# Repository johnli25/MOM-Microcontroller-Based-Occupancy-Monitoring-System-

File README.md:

# Microcontroller-based Occupancy Monitoring (MOM)

### *Won ECE Senior Design Runner-Up Award* (Fall 2022)

## Authors and Acknowledgements
ECE 445 FA2022 Team 7:
- Franklin Moy
- Vish Gopal Sekar
- John Li
- TA: Hanyin Shao

## About
The goal of this project is to create a web app to allow users to determine how occupied popular study locations are.

## Repository Structure
- [**boards**](boards)
  - Contains KiCad project files for the hardware schematics and PCB layouts.
- [**code**](code)
  - Contains all software created for the project, including those used for RV processes and production code.
- [**models**](models)
  - Contains all custom symbols, footprints, and 3D models used for the hardware and enclosure design.
- [**notebooks**](notebooks)
  - Contains all individual lab notebooks.
 
## Paper/Report
[https://github.com/johnli25/MOM/blob/4fe8f952a4ed27d478e640dd72d3c75059fbbd7b/MOM%20Paper.pdf
](https://github.com/johnli25/MOM/blob/main/MOM%20Paper.pdf)
## The web app/dashboard

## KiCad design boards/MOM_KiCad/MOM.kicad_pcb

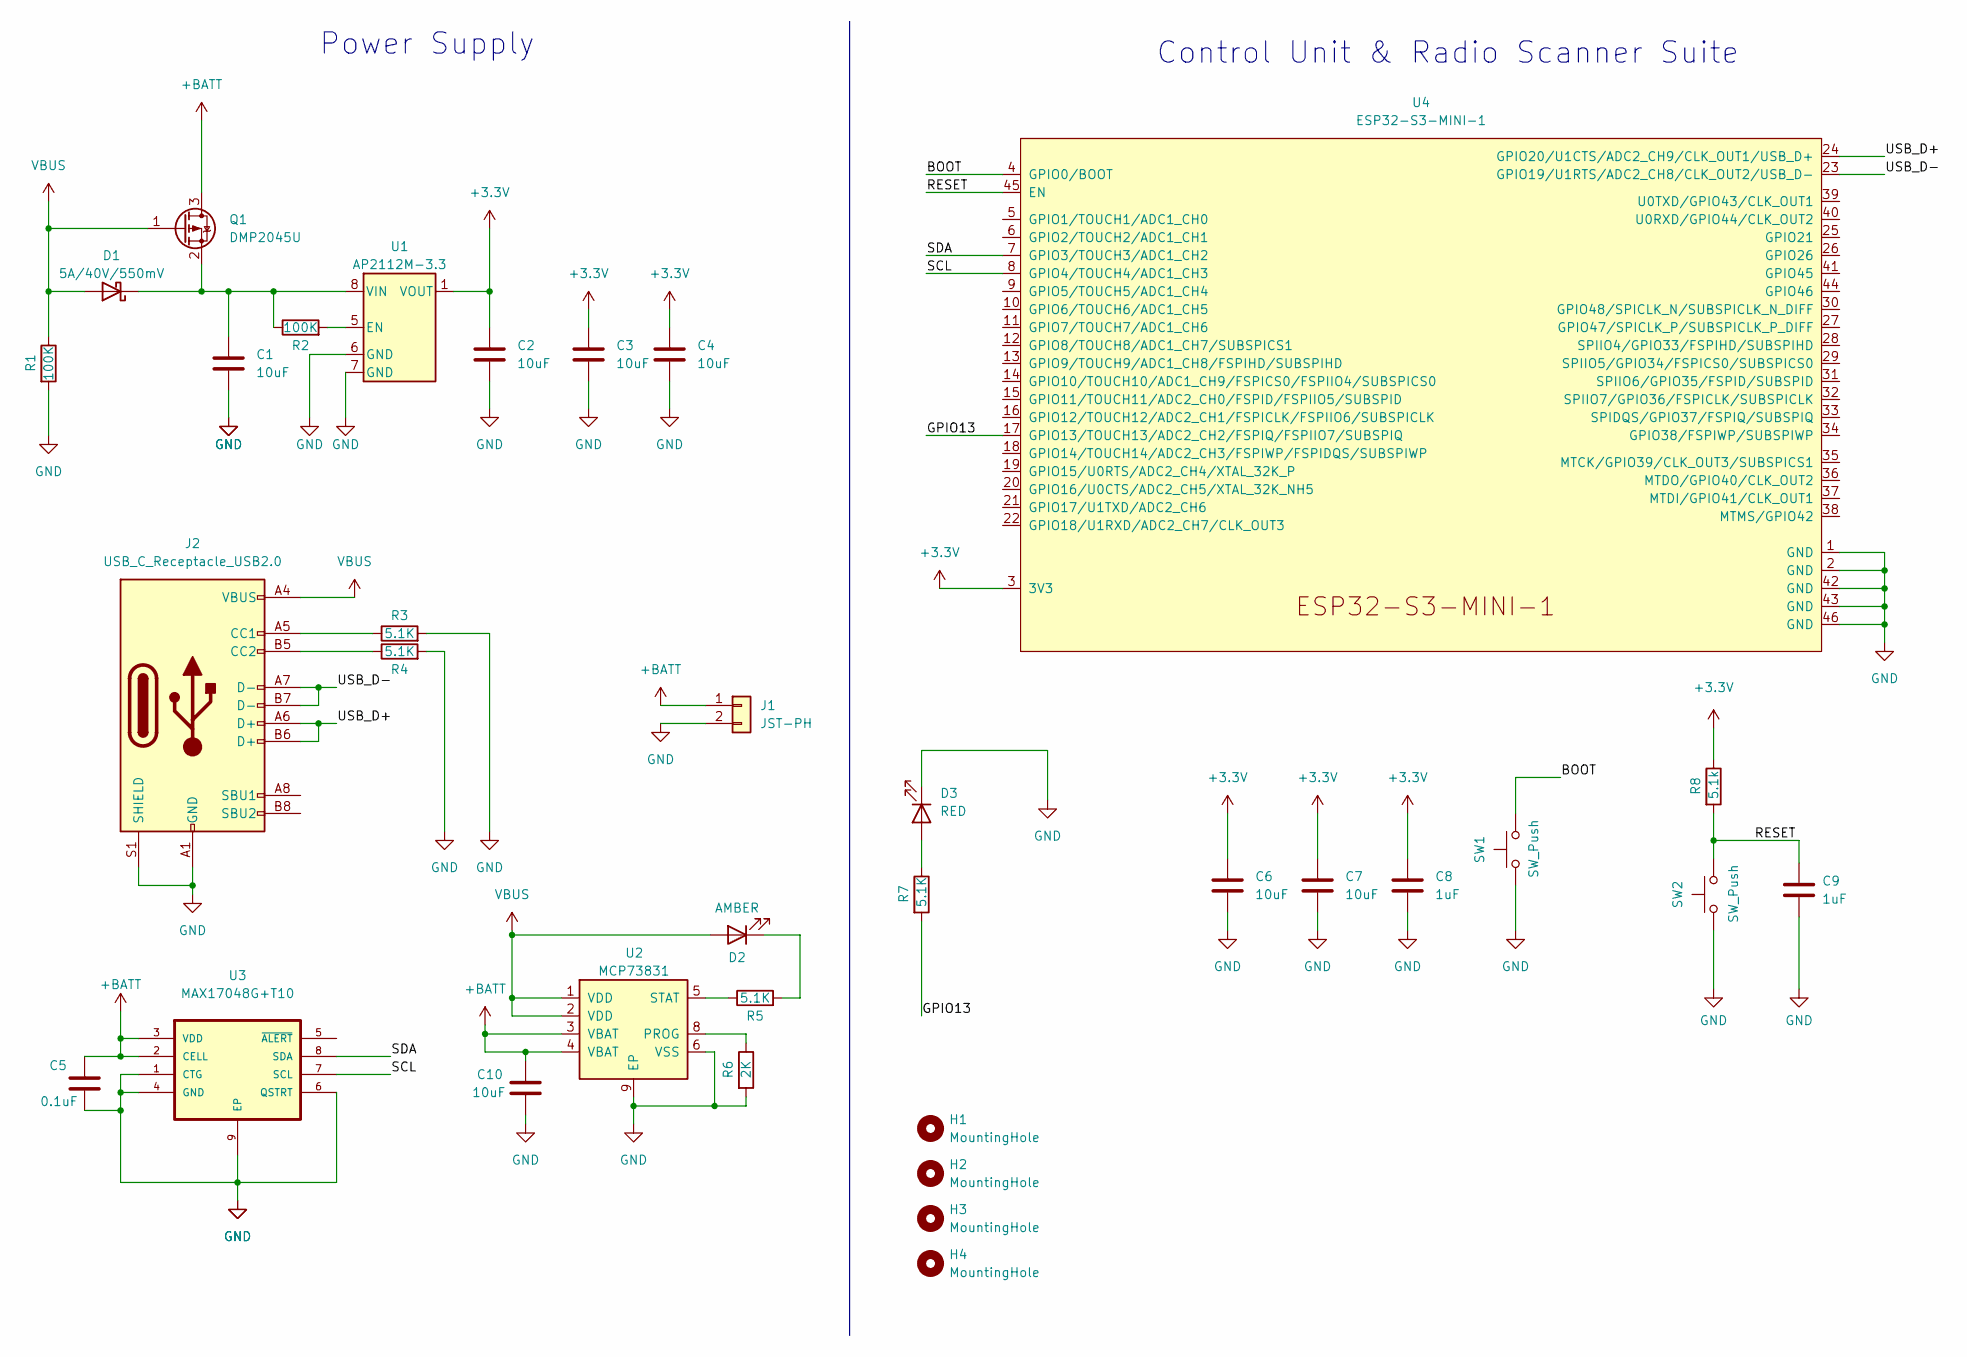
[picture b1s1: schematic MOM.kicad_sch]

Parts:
C1, C2, C3, C4, C6, C7, C10: 10uF; CP_EIA-2012-12_Kemet-R_Pad1.30x1.05mm_HandSolder
C5: 0.1uF; CP_EIA-2012-12_Kemet-R_Pad1.30x1.05mm_HandSolder
C8, C9: 1uF; CP_EIA-2012-12_Kemet-R_Pad1.30x1.05mm_HandSolder
D1: 5A/40V/550mV; D_SMBF_Handsoldering
D2: AMBER; LED_D5.0mm
D3: RED; LED_D5.0mm
H1, H2, H3, H4: MountingHole; MountingHole_3.2mm_M3
J1: JST-PH; JST_PH_S2B-PH-K_1x02_P2.00mm_Horizontal
J2: USB_C_Receptacle_USB2.0; USB_C_Receptacle_GCT_USB4085
Q1: DMP2045U; SOT-23_Handsoldering
R1, R2: 100K; R_1206_3216Metric_Pad1.30x1.75mm_HandSolder
R3, R4, R5, R7: 5.1K; R_1206_3216Metric_Pad1.30x1.75mm_HandSolder
R6: 2K; R_1206_3216Metric_Pad1.30x1.75mm_HandSolder
R8: 5.1k; R_1206_3216Metric_Pad1.30x1.75mm_HandSolder
SW1, SW2: SW_Push; SW_TS04-66-65-BK-160-SMT
U1: AP2112M-3.3; Diodes_SO-8
U2: MCP73831; SON50P200X300X100-9N
U3: MAX17048G+T10; SON50P200X200X80-9N
U4: ESP32-S3-MINI-1

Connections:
+3.3V: C2.1, C3.1, C4.1, C6.1, C7.1, C8.1, R8.1, U1.1 (VOUT), U4.3 (3V3)
+BATT: C5.1, C10.1, J1.1, Q1.3 (D), U2.3 (VBAT), U2.4 (VBAT), U3.2 (CELL), U3.3 (VDD)
/BOOT: SW1.2, U4.4 (GPIO0/BOOT)
/GPIO13: R7.2, U4.17 (GPIO13/TOUCH13/ADC2_CH2/FSPIQ/FSPIIO7/S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)
/RESET: C9.1, R8.2, SW2.2, U4.45 (EN)
/SCL: U3.7 (SCL), U4.8 (GPIO4/TOUCH4/ADC1_CH3)
/SDA: U3.8 (SDA), U4.7 (GPIO3/TOUCH3/ADC1_CH2)
/USB_D+: J2.A6 (D+), J2.B6 (D+), U4.24 (GPIO20/U1CTS/ADC2_CH9/CLK_OUT1/USB_D+)
/USB_D-: J2.A7 (D-), J2.B7 (D-), U4.23 (GPIO19/U1RTS/ADC2_CH8/CLK_OUT2/USB_D-)
GND: C1.2, C2.2, C3.2, C4.2, C5.2, C6.2, C7.2, C8.2, C9.2, C10.2, D3.1 (K), J1.2, J2.A1 (GND), J2.A12 (GND), J2.B1 (GND), J2.B12 (GND), J2.S1 (SHIELD), R1.2, R3.2, R4.2, R6.2, SW1.1, SW2.1, U1.6 (GND), U1.7 (GND), U2.6 (VSS), U2.9 (EP), U3.1 (CTG), U3.4 (GND), U3.6 (QSTRT), U3.9 (EP), U4.1 (GND), U4.2 (GND), U4.42 (GND), U4.43 (GND), U4.46 (GND)
unnamed: C1.1, D1.1 (K), Q1.2 (S), R2.1, U1.8 (VIN)
unnamed: D2.1 (K), R5.2
unnamed: D3.2 (A), R7.1
unnamed: J2.A5 (CC1), R3.1
unnamed: J2.B5 (CC2), R4.1
unnamed: R2.2, U1.5 (EN)
unnamed: R5.1, U2.5 (STAT)
unnamed: R6.1, U2.8 (PROG)
VBUS: D1.2 (A), D2.2 (A), J2.A4 (VBUS), J2.A9 (VBUS), J2.B4 (VBUS), J2.B9 (VBUS), Q1.1 (G), R1.1, U2.1 (VDD), U2.2 (VDD)

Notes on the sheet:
Power Supply
Control Unit & Radio Scanner Suite

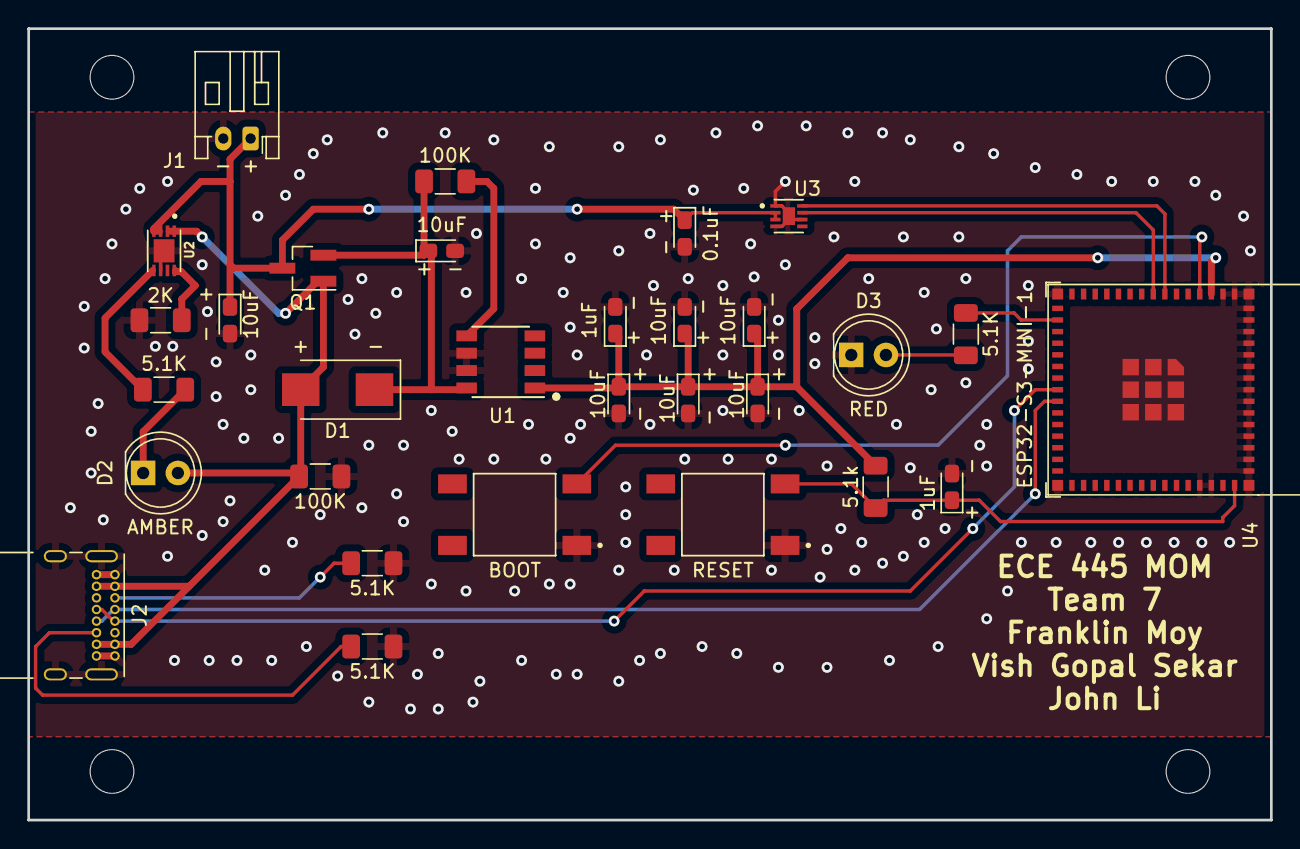
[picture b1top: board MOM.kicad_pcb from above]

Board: 2 copper layers, 90.9 x 57.9 mm, 34 parts (0 on the bottom side), 19 nets.

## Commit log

2022-09-14 Added notebook entry
2022-09-19 Update Vish's Notebook
2022-09-20 Update John's ntbk 9/20/2022
2022-09-25 Notebook additions and First Revision of Schematic
2022-09-27 New schematic revision and repo cleanup
2022-09-30 Schematic updates
2022-10-02 Franklin notebook updates
2022-10-04 PCB version alpha
2022-10-11 Start POC code based off feather
2022-10-12 More groundwork for the POC
2022-10-12 Corrected IDE note
2022-10-12 Update notebook
2022-10-25 Added Aruba OUI list
2022-10-25 Updated notebook
2022-10-25 Squash notebook commits
2022-10-26 OUI and wifi_scanner code
2022-10-31 Ping test and basic AWS code snippets, and added used libraries
2022-11-01 init commit
2022-11-02 Scanner can remember MACs it has seen
2022-11-07 web app occupancy front end
2022-11-07 add comments
2022-11-08 prettified text, titles, and pie chart for web app
2022-11-08 Finished web app front end FIRST TAB-still need to implement multiple tabs for multiple rooms
2022-11-08 updated front end-added battery percentage + more
2022-11-09 worked on connecting to Dynamo
2022-11-09 John pushing from Vish's lapop
2022-11-09 try this
2022-11-13 added links for aws dynamo
2022-11-13 test commit-sanity check
2022-11-13 added config file, rewriting some dynamodb-flask app integration, and created template for database CRUD operations
2022-11-13 cleaned up code-still need to fix AWS credentials-I think have an idea
2022-11-13 code not compiles-now onto LOTS of testing with localhost
2022-11-13 vish run this
2022-11-13 fixed John's clownery
2022-11-13 Added MOM node prod code candidate
2022-11-13 dynamodb database now able to fetch and display data
2022-11-14 Update Franklin notebook
2022-11-14 added 'next room' button
2022-11-14 added implementation for multiple tabs/rooms with a click of a button, added front end prettifications, cleaned up deprecated code and comments, and added more backend functionality. Need to fix relo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
2022-11-15 Migrate to Vish's AWS endpoint
2022-11-16 Backend readaptation and fixed MC not scanning after first message to AWS
2022-11-16 fixed KeyError bug-database 90% working
2022-11-23 Update John's lab notebook
2022-11-23 more work in routes.py, implementing flask web app to pull from latest/most recently updated data in DynamoDB. Need to run more tests to make sure this change works
2022-11-23 finished implementing obtain most recent room data-need to add more tests, data to db, and address assumptions
2022-11-24 11/23/2022 work-bug fixes and extra changes.
2022-11-26 updated database parsing logic/implementation to cover for more edge cases
2022-11-26 front end .html edits
2022-11-27 more finished product work
2022-11-27 deploy/test this
2022-11-28 Update notebook entries
2022-11-29 Adjusting params for prod code
2022-11-29 Beanstalk configuration
2022-11-29 make web app more reactive
2022-11-29 john clow
2022-11-29 updated database indexing
2022-11-29 updated location
2022-11-30 Changed date to reflect database instead of client time
2022-11-30 Set timezone to CT
2022-11-30 full_Count
2022-11-30 Added reappearance factor
2022-11-30 More tuning and algo work
2022-12-08 Notebook update
